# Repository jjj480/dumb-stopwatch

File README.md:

# dumb-stopwatch
its a stopwatch without a microcontroller only with ics. The time displayed on 4 7 Segment displays and goes up one hour.

i wanted to try some othor method to electric things than with a microcontroller. And found that a stoppwatch is not to dificult

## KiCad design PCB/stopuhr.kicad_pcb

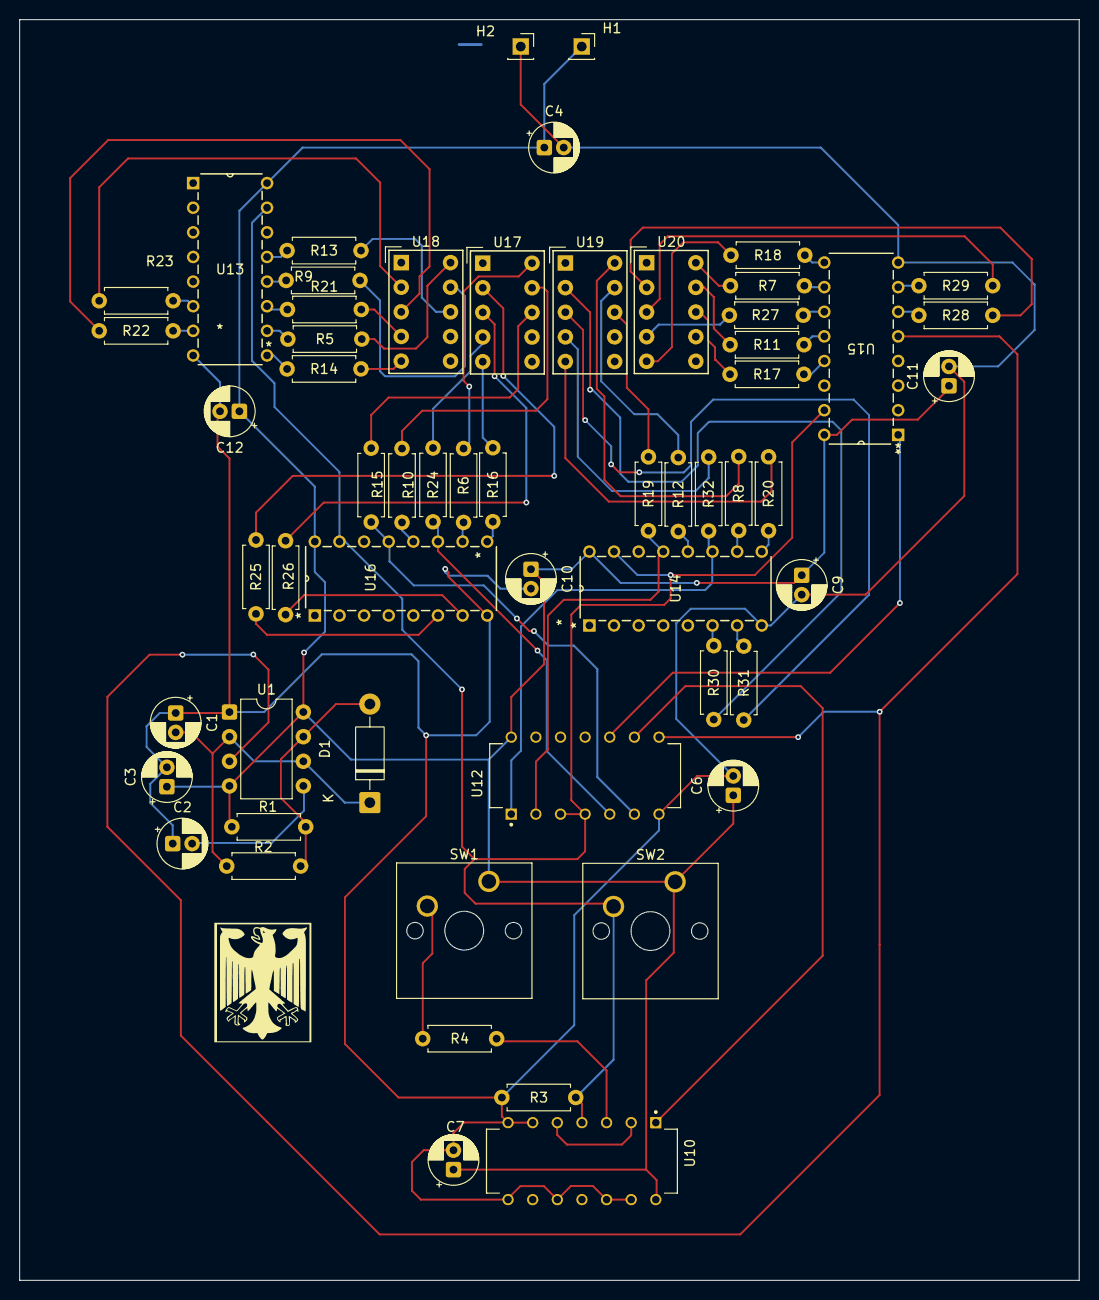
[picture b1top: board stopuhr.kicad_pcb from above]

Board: 2 copper layers, 109.3 x 130.0 mm, 58 parts (0 on the bottom side), 68 nets.

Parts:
C1: 1uf; CP_Radial_D5.0mm_P2.00mm
C2: 10nf; CP_Radial_D5.0mm_P2.00mm
C3, C4, C6, C7, C9, C10, C11, C12: 100nf; CP_Radial_D5.0mm_P2.00mm
D1: SB160; D_DO-41_SOD81_P10.16mm_Horizontal
H1, H2: MountingHole_Pad; PinSocket_1x01_P2.54mm_Vertical
R1: 680KO; R_Axial_DIN0207_L6.3mm_D2.5mm_P7.62mm_Horizontal
R2, R3, R4: 10kO; R_Axial_DIN0207_L6.3mm_D2.5mm_P7.62mm_Horizontal
R5, R6, R7, R8, R9, R10, R11, R12, R13, R14, R15, R16, R17, R18, R19, R20, R21, R22, R23, R24, R25, R26, R27, R28, R29, R30, R31, R32: 300O; R_Axial_DIN0207_L6.3mm_D2.5mm_P7.62mm_Horizontal
SW1: Start/stopp; SW_Cherry_MX_1.00u_PCB
SW2: Reset; SW_Cherry_MX_1.00u_PCB
U1: NA555P; DIP-8_W7.62mm
U10: CD4013BE; DIP794W45P254L1969H508Q14
U12: CD4081BE; DIP794W45P254L1969H508Q14
U13, U14, U15, U16: CD4026BE; N16
U17, U18, U19, U20: HDSP-7401

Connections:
6,1: R32.1, U12.1 (A), U14.11 (E)
6,2: R19.1, U12.2 (B), U14.13 (C)
6,r: R3.1, SW2.2, U10.4 (RESET1), U12.3 (J=A.B), U12.4 (K=C.D), U13.15 (RESET), U14.15 (RESET), U15.15 (RESET), U16.15 (RESET)
60,1: R24.1, U12.5 (C), U16.11 (E)
60,2: R15.1, U12.6 (D), U16.13 (C)
+5V: C3.1, C4.1, C6.1, C7.1, C9.1, C10.1, C11.1, C12.1, H1.1, R1.1, SW1.1, SW2.1, U1.4 (R), U1.8 (VCC), U10.14 (VDD), U12.14 (VDD), U13.16 (VDD), U14.16 (VDD), U15.16 (VDD), U16.16 (VDD)
GND: C1.1, C2.1, C3.2, C4.2, C6.2, C7.2, C9.2, C10.2, C11.2, C12.2, H2.1, R3.2, U1.1 (GND), U10.6 (SET1), U10.7 (VSS), U10.8 (SET2), U10.10 (RESET2), U10.12 (~Q2), U10.13 (Q2), U12.7 (VSS), U13.8 (VSS), U14.8 (VSS), U15.8 (VSS), U16.8 (VSS)
unnamed: D1.2 (A), R1.2, R2.2, U1.7 (DIS)
unnamed: C1.2, D1.1 (K), R2.1, U1.2 (TR), U1.6 (THR)
unnamed: R4.2, SW1.2
unnamed: C2.2, U1.5 (CV)
unnamed: R4.1, U10.3 (CLOCK1)
unnamed: U10.2 (~Q1), U10.5 (D1)
unnamed: R5.1, U13.10 (A)
unnamed: R9.1, U13.12 (B)
unnamed: R13.1, U13.13 (C)
unnamed: R14.1, U13.9 (D)
unnamed: R21.1, U13.11 (E)
unnamed: R23.1, U13.6 (F)
unnamed: R22.1, U13.7 (G)
unnamed: R8.1, U14.10 (A)
unnamed: R12.1, U14.12 (B)
unnamed: R20.1, U14.9 (D)
unnamed: R30.1, U14.6 (F)
unnamed: R31.1, U14.7 (G)
unnamed: R7.1, U15.10 (A)
unnamed: R11.1, U15.12 (B)
unnamed: R17.1, U15.13 (C)
unnamed: R18.1, U15.9 (D)
unnamed: R27.1, U15.11 (E)
unnamed: R28.1, U15.6 (F)
unnamed: R29.1, U15.7 (G)
unnamed: R6.1, U16.10 (A)
unnamed: R10.1, U16.12 (B)
unnamed: R16.1, U16.9 (D)
unnamed: R25.1, U16.6 (F)
unnamed: R26.1, U16.7 (G)
unnamed: R6.2, U17.10 (A)
unnamed: R10.2, U17.9 (B)
unnamed: R15.2, U17.8 (C)
unnamed: R16.2, U17.5 (D)
unnamed: R24.2, U17.4 (E)
unnamed: R25.2, U17.2 (F)
unnamed: R26.2, U17.3 (G)
unnamed: R5.2, U18.10 (A)
unnamed: R9.2, U18.9 (B)
unnamed: R13.2, U18.8 (C)
unnamed: R14.2, U18.5 (D)
unnamed: R21.2, U18.4 (E)
unnamed: R23.2, U18.2 (F)
unnamed: R22.2, U18.3 (G)
unnamed: R8.2, U19.10 (A)
unnamed: R12.2, U19.9 (B)
unnamed: R19.2, U19.8 (C)
unnamed: R20.2, U19.5 (D)
unnamed: R32.2, U19.4 (E)
unnamed: R30.2, U19.2 (F)
unnamed: R31.2, U19.3 (G)
unnamed: R7.2, U20.10 (A)
unnamed: R11.2, U20.9 (B)
unnamed: R17.2, U20.8 (C)
unnamed: R18.2, U20.5 (D)
unnamed: R27.2, U20.4 (E)
unnamed: R28.2, U20.2 (F)
unnamed: R29.2, U20.3 (G)
Out: U1.3 (Q), U12.8 (E), U15.5 (CARRY_OUT)
Q: U10.1 (Q1), U12.9 (F)
signal 1: U12.10 (L=E.F), U15.1 (CLK)
